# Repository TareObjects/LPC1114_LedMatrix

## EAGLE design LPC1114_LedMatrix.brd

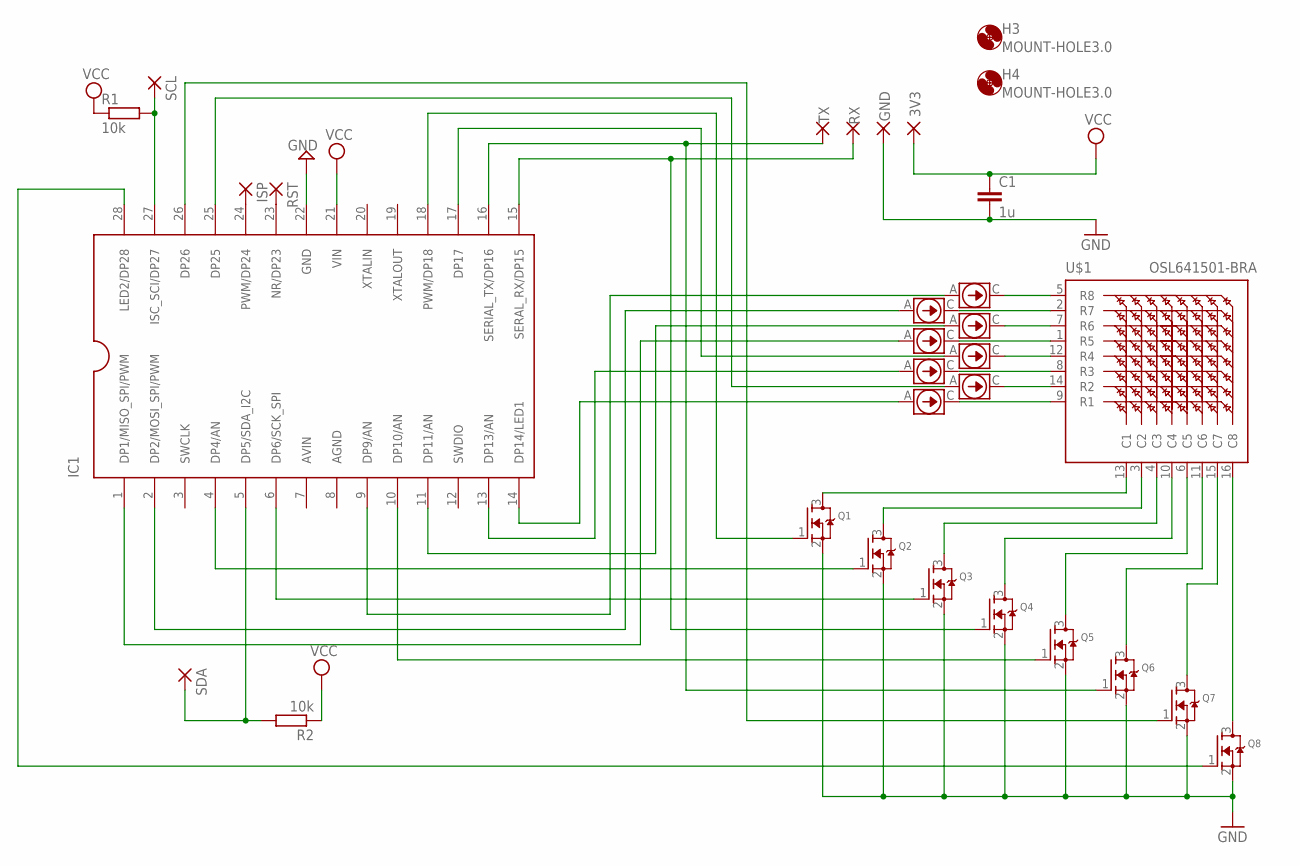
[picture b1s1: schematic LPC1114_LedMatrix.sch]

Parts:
3V3: 1,6/0,8
C1: 1u; C0603
CRD1, CRD2, CRD3, CRD4, CRD5, CRD6, CRD7, CRD8: NSI45020AT1G; SOD-123
GND: 1,6/0,8
H3, H4: MOUNT-HOLE3.0; 3,0
IC1: LPC1114FN28; DIP28
ISP: 1,6/0,8
Q1, Q2, Q3, Q4, Q5, Q6, Q7, Q8: MOSFET-NREFLOW; SOT23
R1, R2: 10k; R0603
RST: 1,6/0,8
RX: 1,6/0,8
SCL: 1,6/0,8
SDA: 1,6/0,8
TX: 1,6/0,8
U$1: OSL641501-BRA; OSL641501

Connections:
AGND: IC1.8 (AGND)
AVIN: IC1.7 (AVIN)
GND: C1.2, GND.1, IC1.22 (GND), Q1.2 (S), Q2.2 (S), Q3.2 (S), Q4.2 (S), Q5.2 (S), Q6.2 (S), Q7.2 (S), Q8.2 (S)
unnamed: CRD8.C, U$1.5 (R8)
unnamed: IC1.10 (DP10/AN), Q5.1 (G)
unnamed: CRD7.C, U$1.2 (R7)
unnamed: CRD1.A, IC1.14 (DP14/LED1)
unnamed: CRD6.C, U$1.7 (R6)
unnamed: IC1.4 (DP4/AN), Q2.1 (G)
unnamed: IC1.6 (DP6/SCK_SPI), Q3.1 (G)
unnamed: CRD5.C, U$1.1 (R5)
unnamed: IC1.5 (DP5/SDA_I2C), R2.2, SDA.1
unnamed: IC1.28 (LED2/DP28), Q8.1 (G)
unnamed: CRD6.A, IC1.11 (DP11/AN)
unnamed: CRD4.C, U$1.12 (R4)
unnamed: IC1.15 (SERAL_RX/DP15), Q4.1 (G), RX.1
unnamed: CRD3.C, U$1.8 (R3)
unnamed: CRD7.A, IC1.2 (DP2/MOSI_SPI/PWM)
unnamed: CRD5.A, IC1.1 (DP1/MISO_SPI/PWM)
unnamed: IC1.24 (PWM/DP24), ISP.1
unnamed: IC1.23 (NR/DP23), RST.1
unnamed: Q8.3 (D), U$1.16 (C8)
unnamed: Q1.3 (D), U$1.13 (C1)
unnamed: CRD2.C, U$1.14 (R2)
unnamed: CRD1.C, U$1.9 (R1)
unnamed: CRD3.A, IC1.13 (DP13/AN)
unnamed: Q2.3 (D), U$1.3 (C2)
unnamed: IC1.16 (SERIAL_TX/DP16), Q6.1 (G), TX.1
unnamed: IC1.27 (ISC_SCI/DP27), R1.2, SCL.1
unnamed: Q3.3 (D), U$1.4 (C3)
unnamed: CRD8.A, IC1.9 (DP9/AN)
unnamed: Q4.3 (D), U$1.10 (C4)
unnamed: Q5.3 (D), U$1.6 (C5)
unnamed: IC1.26 (DP26), Q7.1 (G)
unnamed: CRD2.A, IC1.25 (DP25)
unnamed: IC1.18 (PWM/DP18), Q1.1 (G)
unnamed: Q7.3 (D), U$1.15 (C7)
unnamed: CRD4.A, IC1.17 (DP17)
unnamed: Q6.3 (D), U$1.11 (C6)
VCC: 3V3.1, C1.1, IC1.21 (VIN), R1.1, R2.1

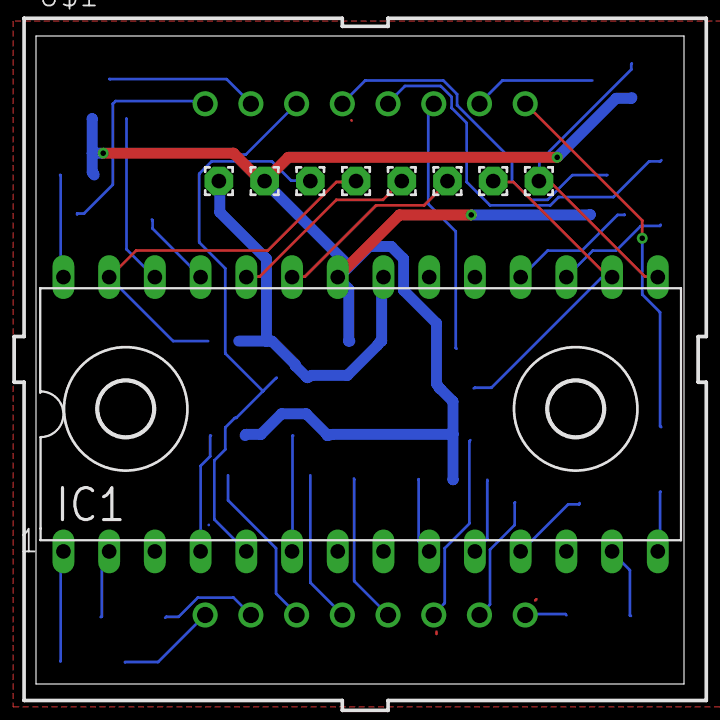
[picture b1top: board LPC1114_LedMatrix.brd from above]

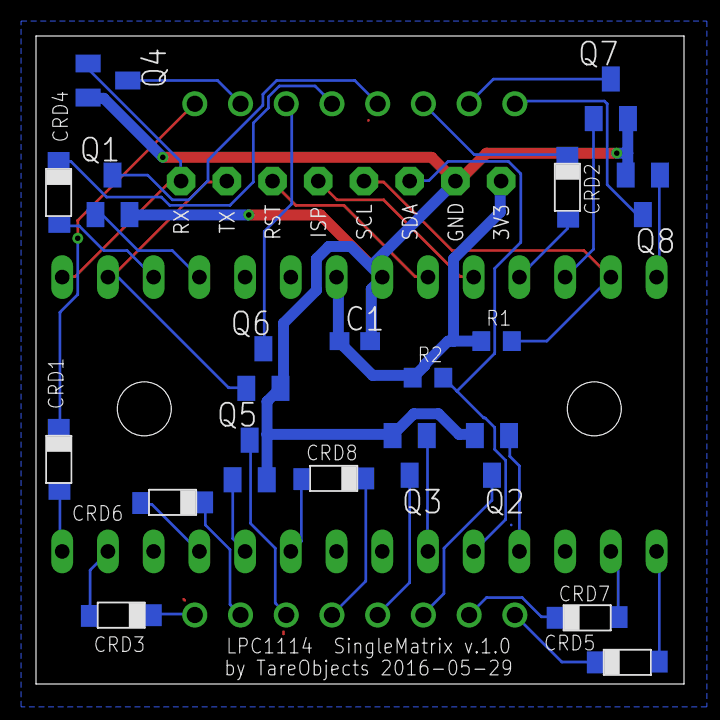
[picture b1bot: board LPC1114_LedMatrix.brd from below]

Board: 2 copper layers, 36.0 x 36.0 mm, 31 parts (19 on the bottom side), 38 nets.
